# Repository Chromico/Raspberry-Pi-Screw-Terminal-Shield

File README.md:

# Raspberry-Pi-Screw-Terminal-Shield

The raspberry pi pin header shield lets you use the raspberry pi pin headers without having to use dupont cables which can vary in quality. The shield lets you use different types of wires/cables and helps make connections to sensors, actuators and so on without the need to solder. The shield is designed to fit onto most raspberry pi boards out there.
The project is open-source hardware and designed with KiCad which makes it a lot easier for the user to modify.

My website: https://tecknologg.website

Blog post: coming soon

# Assembled board

# Documentation
You can get the official documentation here: https://github.com/Chromico/Raspberry-Pi-Screw-Terminal-Shield/blob/main/documentation/Raspberry%20Pi%20Pin%20Header%20Shield%20Documentation.pdf

# Certification
Pending

# Contact

Need to contact me ? Just send me an email at nathan@tecknologg.website or tecknologg@gmail.com

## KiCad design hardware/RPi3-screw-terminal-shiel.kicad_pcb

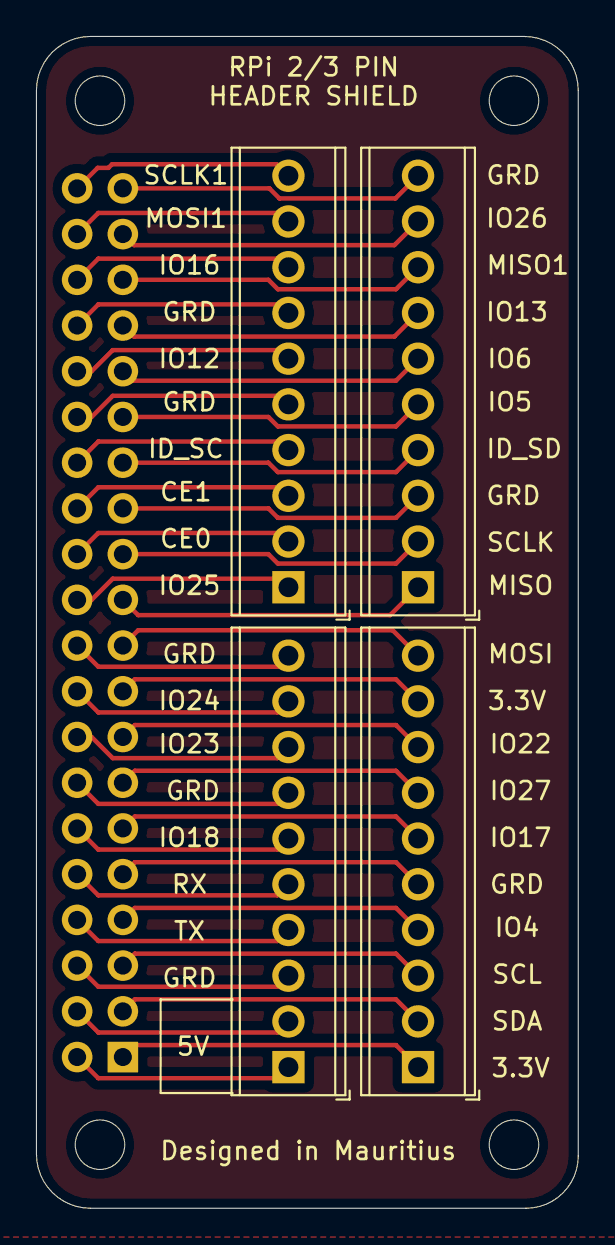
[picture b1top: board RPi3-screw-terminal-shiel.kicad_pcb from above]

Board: 2 copper layers, 30.1 x 65.1 mm, 5 parts (1 on the bottom side), 40 nets.

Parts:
J1: Raspberry_Pi_2_3; Raspberry_Pi_Zero_Socketed_THT_FaceDown_MountingHoles
J2: Left1; TerminalBlock_Phoenix_MPT-0,5-10-2.54_1x10_P2.54mm_Horizont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
J3: Left2; TerminalBlock_Phoenix_MPT-0,5-10-2.54_1x10_P2.54mm_Horizont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
J4: Right1; TerminalBlock_Phoenix_MPT-0,5-10-2.54_1x10_P2.54mm_Horizont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
J5: Right2; TerminalBlock_Phoenix_MPT-0,5-10-2.54_1x10_P2.54mm_Horizont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

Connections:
/1: J1.1, J2.1
/2: J1.2, J4.1
/3: J1.3, J2.2
/4: J1.4, J4.2
/5: J1.5, J2.3
/6: J1.6, J4.3
/7: J1.7, J2.4
/8: J1.8, J4.4
/9: J1.9, J2.5
/10: J1.10, J4.5
/11: J1.11, J2.6
/12: J1.12, J4.6
/13: J1.13, J2.7
/14: J1.14, J4.7
/15: J1.15, J2.8
/16: J1.16, J4.8
/17: J1.17, J2.9
/18: J1.18, J4.9
/19: J1.19, J2.10
/20: J1.20, J4.10
/21: J1.21, J3.1
/22: J1.22, J5.1
/23: J1.23, J3.2
/24: J1.24, J5.2
/25: J1.25, J3.3
/26: J1.26, J5.3
/27: J1.27, J3.4
/28: J1.28, J5.4
/29: J1.29, J3.5
/30: J1.30, J5.5
/31: J1.31, J3.6
/32: J1.32, J5.6
/33: J1.33, J3.7
/34: J1.34, J5.7
/35: J1.35, J3.8
/36: J1.36, J5.8
/37: J1.37, J3.9
/38: J1.38, J5.9
/39: J1.39, J3.10
/40: J1.40, J5.10

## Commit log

2021-07-27 Update LICENSE
